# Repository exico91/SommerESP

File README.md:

# 🏠 SommerESP

A plug and play ESP32-C3 board to control Sommer garage doors based on ESPHOME

This combo is designed to replace the Sommer Conex Module and the Sommer Output OC Module. 

> [!TIP]
> **Where to get in touch**
> - 🐛 **Issues:** [report a problem or suggest an improvement](https://github.com/exico91/SommerESP/issues) for the board.
> - 💬 **Discussions:** [ask a question or share a compatibility report](https://github.com/exico91/SommerESP/discussions).

## ⚙️ How it works
The Sommer Conex Module is designed to replicate the press of the buttons on the controller of the garage door and the Sommer Output OC just provide the signal for the status and 24 Volts DC.  

This project takes the 24V and converts it to 3.3V for the ESP32-C3 module, the DC regulator on the power board can take from 4.5V to 40V and cleanly output 3.3V then transfer it to the Control board along with the status signal.  

The ESP controller simulate the press of the buttons using a pair of optocouplers, simple enough. You can also attach other things to this board, I left a couple of GPIOs on exposed pins along with the serial connection required to flash the module.

## 📋 Instructions
You can buy [here](https://www.tindie.com/products/exico91/sommeresp/) the kit that includes the two boards and a cable or you can build one yourself. You can find the BOM (bill of materials) [here](https://htmlpreview.github.io/?https://github.com/exico91/SommerESP/blob/main/Kicad/SommerESP/bom/ibom.html) and the gerber files [here](/Kicad/SommerESP/gerbers/). 
There are a lot of PCB Manufacturers. The most known are [PCBWay](https://www.pcbway.com/) and [JLCPCB](https://jlcpcb.com/). I used both and are good.

### 🔧 Installation
 1. Remove the plug from the wall, or cut off power to the Sommer garage door controller
 2. Write your firmware if you want or use it as is. You can find a basic yaml [here](/ESPHOME/esphome.yaml) or the ethernet module variant [here](/ESPHOME/esphome-eth.yaml). To do so you will need a serial programmer and set it to 3.3V, connect GND, VIN, RX and TX to the controller board and power it on while pressing BOOT on the board. When you are done remove the serial programmer. DO NOT connect the programmer while the board is connected to the power board or inserted in the Sommer controller.
 3. Open the controller but pay attention to the keypad cable when you remove the cover
 4. Place the board as shown, pay attention that both plugs are inserted:

 5. Flip the first two switches to ON on the dip switch array on the Sommer controller
 6. Connect the keypad to the board in the same orientation as it was before (if present, some Sommers do not have a keypad)
 7. Close the cover and power it on. You should be able to see a wifi network and connect to it to configure the module.

> [!NOTE]
> The ethernet module (W5500) yaml is available [here](/ESPHOME/esphome-eth.yaml) and the KiCad project [here](/Kicad/SommerESP-ETHmodule/).

### 📡 External Antenna

If your installation requires better WiFi reception, an external antenna version is available. You will need:
 1. The SommerESP board in the version **without integrated antenna**, available on the [Tindie store](https://www.tindie.com/stores/exico91/)
 2. The **antenna kit** (includes antenna and U.FL adapter cable), also available on the [Tindie store](https://www.tindie.com/stores/exico91/)

Connect the adapter cable to the U.FL connector on the board and attach the external antenna.

### 🛠️ Settings

#### Door position (%)
> [!NOTE]
> This setting require firmware version **3.3** or later.

By default the door is shown only as open or closed. Once the travel times are set, the position is shown as a percentage and the door can be moved to a specific position from Home Assistant.

1. With a stopwatch, measure how long the door takes to open fully (from fully closed) and to close fully (from fully open).
2. In Home Assistant open the SommerESP device page and, under **Configuration**, enter the measured values in **Garage door open time** and **Garage door close time** (in seconds, 0.1 s resolution, up to 120 s). The same fields are available on the ESP web page.
3. Close the door fully once, so the estimated position is aligned with the closed endstop.

The percentage is enabled only when both times are set: set either of them to 0 to go back to plain open/closed. The values are saved on the board and survive reboots. You can also set the defaults directly in the yaml with the `door_open_time` and `door_close_time` substitutions.

> [!TIP]
> The position is estimated from the travel times. If the door is moved with the remote or the wall button, the estimate can drift: it is realigned every time the door closes fully.

Still, this uses an estimated position because the motherboard does not communicate the percentage natively.

### 🔌 Flashing and extra pins
To flash connect you serial programmer to the exposed pins on the controller board. DO NOT connect the programmer while the board is connected to the power board or inserted in the Sommer controller.
From top to bottom the pins are in this order:

3.3V
GPIO05
RX
TX
GPIO18
GPIO19
GPIO03
GND

Press BOOT while powering on the programmer to send the controller in flashing mode.

### 🔄 Factory reset
With the provided yaml, holding the BOOT button for 10 seconds and then releasing it factory resets the board (erases the saved Wi-Fi credentials and preferences, then reboots). It can also be triggered from Home Assistant with the "Factory Reset" button.

## ✅ Compatibility
This project should work with Sommer Base+, Pro+ and Evo+.
The main focus of this project is ESPHome and Homeassistant but you can flash whatever you want on the ESP32-C3.
Check [here](/pinout.md) for the pinout.

**Confirmed working models:**

| **Model**  | **Notes**                                                                                                                                                  | **Credits** |
|------------|------------------------------------------------------------------------------------------------------------------------------------------------------------|-------------|
| 9080 Base+ | The keypad plug is present but there is no keypad, just plug the SommerESP there.                                                                          | tim-kiefer  |
| 2060 Evo+  | The keypad plug has 5 pins instead of 3. Just plug the module on the middle leaving pin 1 and 5 free. See photo for reference [here](/pics/2060+notes.jpg) | Severnt     |
| 9110 Pro+  | Original installation that created this project. This model has a wall mount control board with a 2 button keypad.                                         | Alessio D   |
| S 9050 pro | Need to manually add the DIP switch selector. Check [here](https://github.com/exico91/SommerESP/issues/5#issuecomment-2755661908)                     | M3c4tr0x    |
| A800 XL    | Compatible but the Conex pins are shifted. Requires board version 2 or jumper cables.                                                                    | [jkremlacek](https://github.com/jkremlacek) |

Tested SommerESP on another model? Please share your result in [Discussions](https://github.com/exico91/SommerESP/discussions), whether it worked or not.

> [!WARNING]
> Please do check the distance between the power pins and the right pin on the button connector. This version of SommerESP is compatible with Sommer boards where the distance is around 9.5 mm or 7.5 mm, just check which is correct and solder the connector for the Conex section in the 9.5 (default) or 7.5 place. If you are buying from Tindie the default will be 9.5, if you need 7.5 please contact me.

## 📦 Release Log

### Firmware Release Log

| **Version** | **ESPHome** | **Changes** |
|-------------|-------------|-------------|
| 1.0 | — | Initial release |
| 1.3 | 2024.6.1 | Added compatibility for ESPHome 2024.6.1 |
| 2.0 | 2025.8.3 | Added compatibility for ESPHome 2025.8.3 |
| 3.0 | 2026.5.3 | Added compatibility for ESPHome 2026.5.3+, added Ethernet module version |
| 3.1 | 2026.5.3 | Cover stop function is now working |
| 3.2 | 2026.9.0 | Added factory reset function to the BOOT button (hold for 10 seconds) |
| 3.3 | 2026.10.2 | Added garage door percentage option

### Hardware Release Log

| **Version** | **Changes** |
|-------------|-------------|
| 1.0 - 2.0 | Dual board module with cable |
| 3.0 | Single board, adds Ethernet compatibility. Supports only 9.5 mm distance |
| 3.1 | Adds 7.5 mm distance compatibility |
| 3.2 | Added fabrication holes to the PCB |
| 3.2.1 | Fixed wrong position of J7 |

## 💡 Origins
A thank you to https://github.com/jampez77/garage_door_sensor/ and https://github.com/azrael783/esphome_garagedoor_opener for giving me the ispiration to do this project, a lot of the code and core functionality is similar to these projects. Unfortunately neither did what I needed, cheap and invisible installation. Unfortunately the two Sommer modules (Conex and Output OC) are not cheap for what they are and using a DC-DC converter and relais externally is bulky and unsightly. I took the matter into my hands and now is almost plug and play and places where the two Sommer modules were.

A thank you to [M3c4tr0x](https://github.com/M3c4tr0x) for a part of the design of the new single board.

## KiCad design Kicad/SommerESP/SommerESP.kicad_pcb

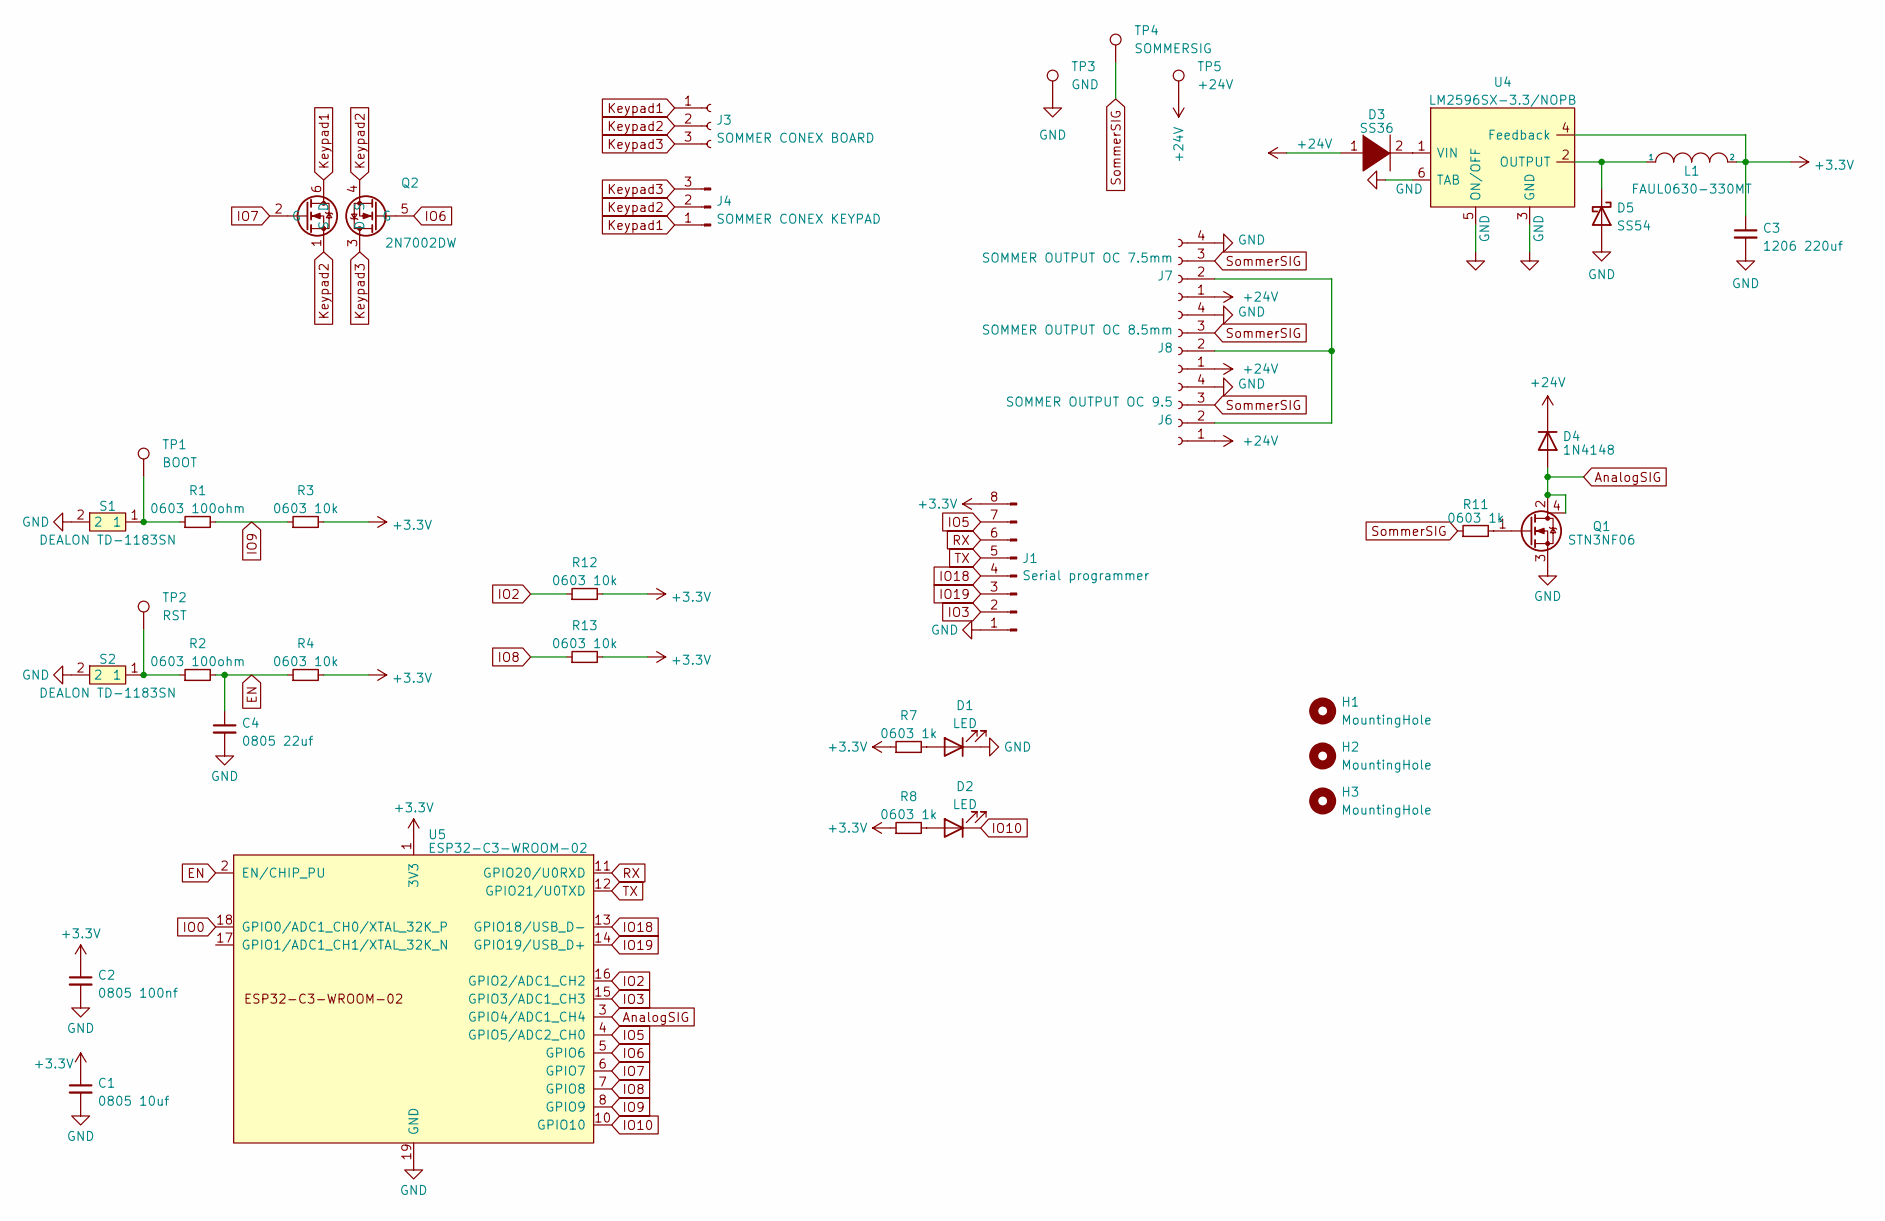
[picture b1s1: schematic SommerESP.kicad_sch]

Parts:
C1: 0805 10uf; C_0805_2012Metric_Pad1.18x1.45mm_HandSolder; LCSC PN C307525
C2: 0805 100nf; C_0805_2012Metric_Pad1.18x1.45mm_HandSolder; LCSC PN C5137467
C3: 1206 220uf; C_1206_3216Metric_Pad1.33x1.80mm_HandSolder; LCSC PN C412252
C4: 0805 22uf; C_0805_2012Metric_Pad1.18x1.45mm_HandSolder; LCSC PN C5674
D1: LED; LED_0805_2012Metric_Pad1.15x1.40mm_HandSolder; LCSC PN C397047
D2: LED; LED_0805_2012Metric_Pad1.15x1.40mm_HandSolder; LCSC PN C497961
D3: SS36; SS32C; LCSC PN C5449114
D4: 1N4148; D_SOD-123; LCSC PN C917030
D5: SS54; D_SMA; LCSC PN C2902914
H1, H2, H3: MountingHole; ToolingHole_1.152mm
J1: Serial programmer; PinHeader_1x08_P2.54mm_Vertical; LCSC PN C6332201
J3: SOMMER CONEX BOARD; PinSocket_1x03_P2.54mm_Vertical; LCSC PN C146243
J4: SOMMER CONEX KEYPAD; PinHeader_1x03_P2.54mm_Vertical; LCSC PN C49257
J6: SOMMER OUTPUT OC 9.5; PinSocket_1x04_P2.54mm_Vertical_SLIT; LCSC PN C2718488
J7: SOMMER OUTPUT OC 7.5mm; PinSocket_1x04_P2.54mm_Vertical_SLIT; LCSC PN C2718488
J8: SOMMER OUTPUT OC 8.5mm; PinSocket_1x04_P2.54mm_Vertical_SLIT; LCSC PN C2718488
L1: FAUL0630-330MT; L_Abracon_ASPI-0630LR; LCSC PN C7461364
Q1: STN3NF06; STN3NF06L; LCSC PN C222218
Q2: 2N7002DW; SOT-363_SC-70-6; LCSC PN C5190214
R1, R2: 0603 100ohm; R_0603_1608Metric_Pad0.98x0.95mm_HandSolder; LCSC PN C3017758
R3, R4, R12, R13: 0603 10k; R_0603_1608Metric_Pad0.98x0.95mm_HandSolder; LCSC PN C2930027
R7, R8, R11: 0603 1k; R_0603_1608Metric_Pad0.98x0.95mm_HandSolder; LCSC PN C116692
S1, S2: DEALON TD-1183SN; DEALON TD-1183SN-1.5H-160; LCSC PN C2905192
TP1: BOOT; TestPoint_Pad_2.0x2.0mm
TP2: RST; TestPoint_Pad_2.0x2.0mm
TP3: GND; TestPoint_Pad_D2.0mm
TP4: SOMMERSIG; TestPoint_Pad_D2.0mm
TP5: +24V; TestPoint_Pad_D2.0mm
U4: LM2596SX-3.3/NOPB; TO-263-5_TabPin3; LCSC PN C5186052
U5: ESP32-C3-WROOM-02; LCSC PN C2934560

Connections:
+3.3V: C1.1, C2.1, C3.1, J1.8, L1.2, R3.2, R4.2, R7.1, R8.1, R12.2, R13.2, U4.4 (Feedback), U5.1 (3V3)
+24V: D3.1 (K), D4.1 (K), J6.1, J7.1, J8.1, TP5.1 (1_1)
AnalogSIG: D4.2 (A), Q1.2 (D), Q1.4 (D_TAB), U5.3 (GPIO4/ADC1_CH4)
EN: C4.1, R2.2, R4.1, U5.2 (EN/CHIP_PU)
GND: C1.2, C2.2, C3.2, C4.2, D1.1 (K), D5.2 (A), J1.1, J6.4, J7.4, J8.4, Q1.3 (S), S1.2, S2.2, TP3.1 (1_1), U4.3 (GND), U4.5 (ON/OFF), U4.6 (TAB), U5.9 (GND), U5.19 (GND)
IO0: U5.18 (GPIO0/ADC1_CH0/XTAL_32K_P)
IO2: R12.1, U5.16 (GPIO2/ADC1_CH2)
IO3: J1.2, U5.15 (GPIO3/ADC1_CH3)
IO5: J1.7, U5.4 (GPIO5/ADC2_CH0)
IO6: Q2.5 (G), U5.5 (GPIO6)
IO7: Q2.2 (G), U5.6 (GPIO7)
IO8: R13.1, U5.7 (GPIO8)
IO9: R1.2, R3.1, U5.8 (GPIO9)
IO10: D2.1 (K), U5.10 (GPIO10)
IO18: J1.4, U5.13 (GPIO18/USB_D-)
IO19: J1.3, U5.14 (GPIO19/USB_D+)
Keypad1: J3.1, J4.1, Q2.6 (D)
Keypad2: J3.2, J4.2, Q2.1 (S), Q2.4 (S)
Keypad3: J3.3, J4.3, Q2.3 (D)
unnamed: D1.2 (A), R7.2
unnamed: D2.2 (A), R8.2
unnamed: D3.2 (A), U4.1 (VIN)
unnamed: D5.1 (K), L1.1, U4.2 (OUTPUT)
unnamed: J6.2, J7.2, J8.2
unnamed: Q1.1 (G), R11.2
unnamed: R1.1, S1.1, TP1.1 (1_1)
unnamed: R2.1, S2.1, TP2.1 (1_1)
RX: J1.6, U5.11 (GPIO20/U0RXD)
SommerSIG: J6.3, J7.3, J8.3, R11.1, TP4.1 (1_1)
TX: J1.5, U5.12 (GPIO21/U0TXD)

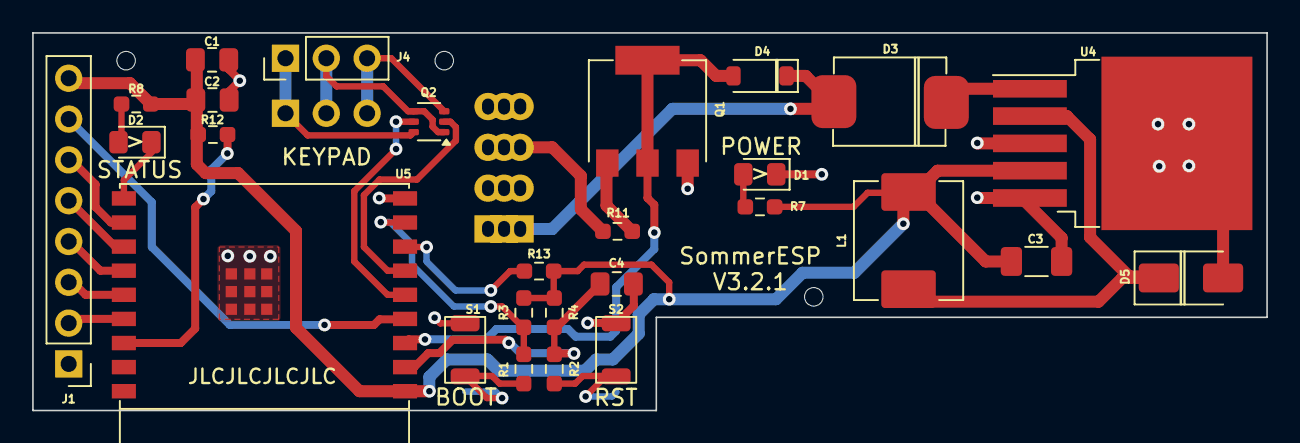
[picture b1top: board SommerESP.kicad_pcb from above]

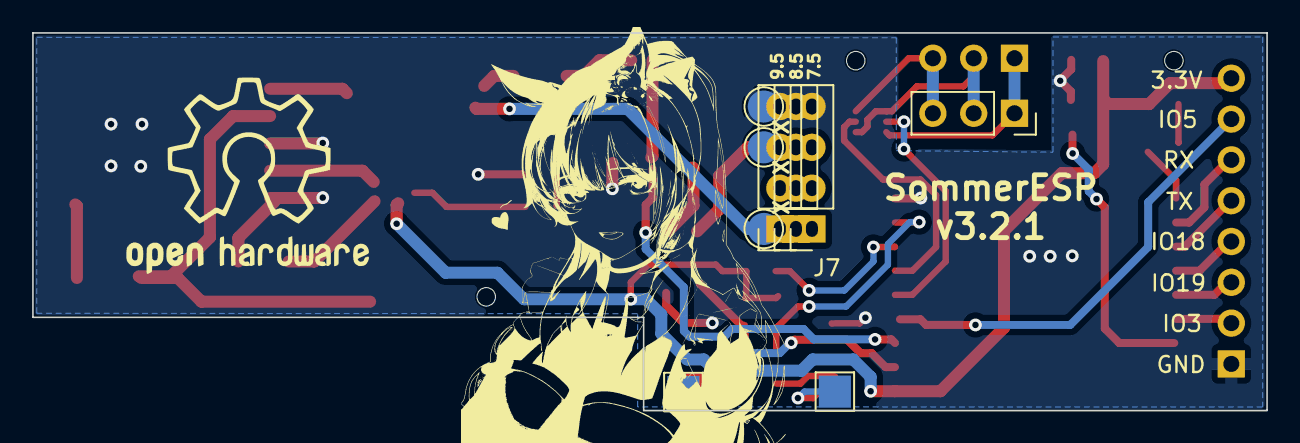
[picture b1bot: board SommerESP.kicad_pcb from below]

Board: 2 copper layers, 76.8 x 23.5 mm, 39 parts (9 on the bottom side), 29 nets.

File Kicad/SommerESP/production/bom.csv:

Designator,Footprint,Quantity,Value,LCSC Part #
C1,0805,1,0805 10uf,C412252
C2,0805,1,0805 100nf,C412252
C3,1206,1,1206 220uf,C412252
C4,0805,1,0805 22uf,C412252
D1,0805,1,LED Green,C397047
D2,0805,1,LED Blue,C497961
D3,SS32C,1,SS36,C5449114
D4,D_SOD-123,1,1N4148,C402212
D5,D_SMA,1,SS54,C2902914
J1,PinHeader_1x08_P2.54mm_Vertical,1,Serial programmer,C6332201
J3,PinSocket_1x03_P2.54mm_Vertical,1,SOMMER CONEX BOARD,C146243
J4,PinHeader_1x03_P2.54mm_Vertical,1,SOMMER CONEX KEYPAD,C49257
J6,PinSocket_1x04_P2.54mm_Vertical,1,SOMMER OUTPUT OC,C2718488
L1,L_Abracon_ASPI-0630LR,1,FAUL0630-330MT,C7461364
Q1,STN3NF06L,1,STN3NF06,C222218
Q2,SOT-363_SC-70-6,1,2N7002DW,C5190214
"R1, R2",0603,2,0603 100ohm,C3017758
"R11, R7, R8",0603,3,0603 1k,C116692
"R12, R13, R3, R4",0603,4,0603 10k,C2930027
"S1, S2",DEALON TD-1183SN-1.5H-160,2,DEALON TD-1183SN,C2905192
U4,TO-263-5_TabPin3,1,LM2596SX-3.3/NOPB,C5186052
U5,ESP32-C3-WROOM-02,1,ESP32-C3-WROOM-02,C2934560

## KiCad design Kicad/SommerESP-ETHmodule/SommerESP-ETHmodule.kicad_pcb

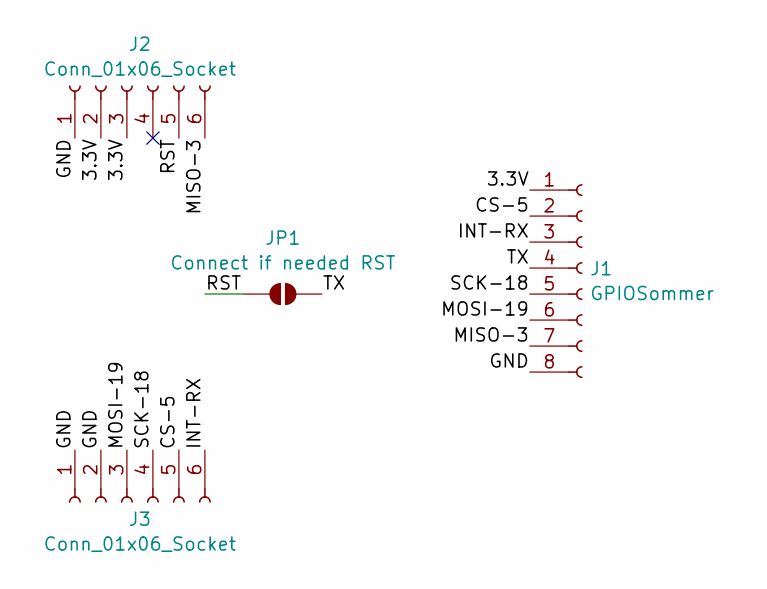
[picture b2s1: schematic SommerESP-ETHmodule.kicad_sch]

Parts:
J1: GPIOSommer; PinSocket_1x08_P2.54mm_Vertical
J2, J3: Conn_01x06_Socket; PinSocket_1x06_P2.54mm_Vertical
JP1: Connect if needed RST; SolderJumper-2_P1.3mm_Open_RoundedPad1.0x1.5mm

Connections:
/3.3V: J1.1, J2.2, J2.3
/CS-5: J1.2, J3.5
/GND: J1.8, J2.1, J3.1, J3.2
/INT-RX: J1.3, J3.6
/MISO-3: J1.7, J2.6
/MOSI-19: J1.6, J3.3
/RST: J2.5, JP1.1 (A)
/SCK-18: J1.5, J3.4
/TX: J1.4, JP1.2 (B)

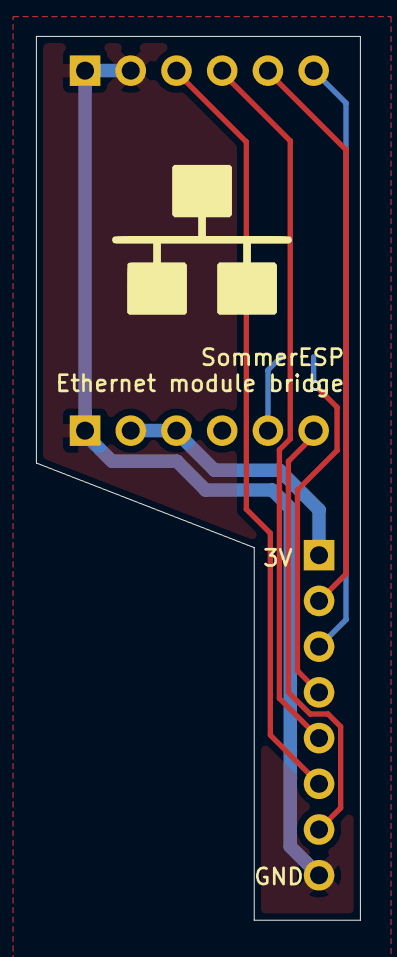
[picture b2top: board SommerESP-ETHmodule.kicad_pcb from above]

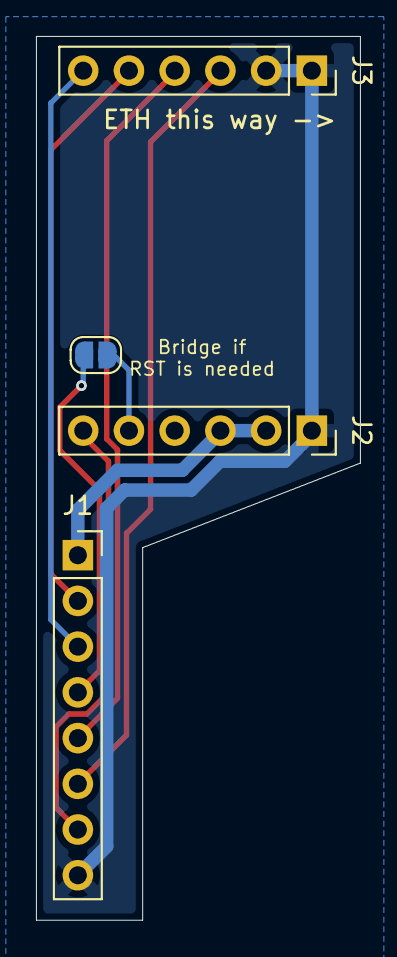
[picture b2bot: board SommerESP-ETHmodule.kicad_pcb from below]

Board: 2 copper layers, 18.0 x 49.1 mm, 4 parts (4 on the bottom side), 9 nets.

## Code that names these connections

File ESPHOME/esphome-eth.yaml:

esphome:
  name: sommeresp-eth
  name_add_mac_suffix: true
  project:
    name: "esphome.sommeresp"
    version: "3.3"

substitutions:
  device_name: "SommerESP"
  hotspot_password: "sommeresp"
  webserver_password: "sommeresp"

  project_name: "SommerESP by exico91"
  project_version: "3.3"

  # Full travel times of the door in seconds, used to estimate its position
  # in %. 0 = not configured: the door is shown only as open/closed. Measure
  # them with a stopwatch; they can also be set later from Home Assistant
  # (Garage door open/close time). The percentage works only when both are set.
  door_open_time: "0"
  door_close_time: "0"


esp32:
  board: esp32-c3-devkitm-1
  framework:
    type: arduino


# Enable logging
logger:

# Enable Home Assistant API
api:

ota:
  - platform: esphome

ethernet:
  type: W5500
  clk_pin: GPIO18
  mosi_pin: GPIO19
  miso_pin: GPIO3
  cs_pin: GPIO5
  interrupt_pin: GPIO20

# Optional Static IP
#  manual_ip: 
#    static_ip: 192.168.1.60
#    gateway: 192.168.1.1
#    subnet: 255.255.255.0
    
# Enable Web server (optional).
web_server:
  port: 80

# Uncomment to setup user and password for the dashboard
#  auth:
#    username: "admin"
#    password: ${webserver_password}


text_sensor:
  # Expose ESPHome version as sensor.
  - platform: version
    name: ${device_name} ESPHome Version
  # Expose Ethernet information
  - platform: ethernet_info
    ip_address:
      name: ESP IP Address 
    dns_address: 
      name: ESP DNS Address
    mac_address: 
      name: ESP MAC Address
    
sensor:
  - platform: uptime
    name: ${device_name} Uptime
  - platform: adc
    pin: 4
    name: "Door Feedback"
    update_interval: 500ms
    id: status_feedback
    internal: True

binary_sensor:
  # ON when the door is fully closed: used as the close endstop of the cover.
  - platform: analog_threshold
    name: "Door closed"
    sensor_id: status_feedback
    threshold: 0.015
    id: door_closed
    internal: True
    on_release:
      # The door left the closed position without a command from us (remote,
      # wall button): its movement can't be tracked, so assume fully open.
      - lambda: |-
          if (id(garage_door).current_operation == COVER_OPERATION_IDLE) {
            id(garage_door).position = COVER_OPEN;
            id(garage_door).publish_state();
          }

  # BOOT button: hold for 10s to factory reset. It acts on release, so the
  # reboot never happens with GPIO9 held low (which would enter download mode).
  - platform: gpio
    pin:
      number: GPIO9
      mode: INPUT_PULLUP
      inverted: true
    id: boot_button
    internal: true
    on_click:
      min_length: 10s
      max_length: 60s
      then:
        - button.press: factory_reset_button

globals:
  - id: last_direction
    type: int
    restore_value: no
    initial_value: '0'  # 0=idle, 1=opening, 2=closing
  - id: move_start
    type: uint32_t
    restore_value: no
    initial_value: '0'  # millis() of the last open/close pulse

number:
  - platform: template
    name: "Garage door open time"
    id: open_time
    entity_category: config
    unit_of_measurement: s
    mode: box
    min_value: 0
    max_value: 120
    step: 0.1
    optimistic: true
    restore_value: true
    initial_value: ${door_open_time}
    on_value:
      - script.execute: apply_travel_times
  - platform: template
    name: "Garage door close time"
    id: close_time
    entity_category: config
    unit_of_measurement: s
    mode: box
    min_value: 0
    max_value: 120
    step: 0.1
    optimistic: true
    restore_value: true
    initial_value: ${door_close_time}
    on_value:
      - script.execute: apply_travel_times

script:
  # With both travel times set, the cover estimates the position from them.
  # Otherwise it moves instantly: open is shown as soon as the door is commanded
  # to open, closed when the status input reports it, as before.
  - id: apply_travel_times
    then:
      - lambda: |-
          bool timed = id(open_time).state > 0 && id(close_time).state > 0;
          id(garage_door).set_open_duration(timed ? id(open_time).state * 1000 : 1);
          id(garage_door).set_close_duration(timed ? id(close_time).state * 1000 : 1);

switch:
  - platform: gpio
    pin: 
      number: 7
      #inverted: True
    name: "Garage door Open Switch"
    id: open_switch
    on_turn_on:
      - delay: 250ms
      - switch.turn_off: open_switch
    restore_mode: ALWAYS_OFF
  - platform: gpio
    pin: 
      number: 6
      #inverted: True
    name: "Garage door close Switch"
    id: close_switch
    on_turn_on:
      - delay: 250ms
      - switch.turn_off: close_switch
    restore_mode: ALWAYS_OFF
  - platform: restart
    name: "Restart ESP"

button:
  - platform: factory_reset
    name: "Factory Reset"
    id: factory_reset_button
    entity_category: diagnostic

cover:
  # Time based cover: the position is estimated from the travel times, and
  # setting a position sends a stop pulse when the estimate reaches it.
  - platform: feedback
    id: garage_door
    device_class: garage
    name: "Garage door"
    # Set at boot from the travel time numbers (apply_travel_times).
    open_duration: 1ms
    close_duration: 1ms
    close_endstop: door_closed
    # The Sommer stops by itself at the ends, never send a stop there.
    has_built_in_endstop: true
    # Reversing while moving: stop first, then start the other way.
    direction_change_wait_time: 1s
    # Give up waiting for the close endstop (e.g. the door reversed on an obstacle).
    max_duration: 150s
    open_action:
      - globals.set:
          id: last_direction
          value: '1'
      - lambda: 'id(move_start) = millis();'
      - switch.turn_off: close_switch
      - switch.turn_on: open_switch
    close_action:
      - globals.set:
          id: last_direction
          value: '2'
      - lambda: 'id(move_start) = millis();'
      - switch.turn_off: open_switch
      - switch.turn_on: close_switch
    # The Sommer stops when it gets another pulse in the direction it is moving.
    # Only pulse while the motor can still be moving: after the full travel time
    # (120s without travel times) it has stopped by itself, and a pulse would
    # start it again.
    stop_action:
      - lambda: |-
          if (id(last_direction) == 0)
            return;
          bool opening = id(last_direction) == 1;
          switch_::Switch *relay = opening ? id(open_switch) : id(close_switch);
          // The command pulse is still on: the stop came right after the command
          // (target already reached without travel times), keep moving.
          if (relay->state)
            return;
          bool timed = id(open_time).state > 0 && id(close_time).state > 0;
          float travel = timed ? (opening ? id(open_time).state : id(close_time).state) : 120;
          if (millis() - id(move_start) < travel * 1000)
            relay->turn_on();
          id(last_direction) = 0;

status_led:
  pin:
    number: 10
    inverted: true
    

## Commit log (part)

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2023-10-09 First upload
2023-10-09 Added instructions
2023-10-21 Updated description and yaml
2023-10-26 removed backups
    inverted up and down pins after testing
2023-11-16 Update README.md
    added link to shop
2023-12-04 Update esphome.yaml
    Added some options and better device naming
2024-01-13 Found an error in the schematic for Diode D4. Was inverted in the schematic but correct in the PCB and Photos.
    Thank you to Stefano Gnocato for pointing that out!
2024-01-25 Updated the check for door status from analog threshold to gpio with a pullup. This should be less prone to error and free some computational power
    Thanks to Stefano Gnocato for the input!
2024-03-17 Updated ota and api, cleaned the code a bit.
2024-05-08 Updated Kicad to version 8 Added references to LCSC part numbers in the project and BOM Cleaned up a bit of silkscreen text and added some references Added JLCJLCJLCJLC on the silkscreen for the orde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
2024-06-21 Compatibility with esphome 2024.6.1 +
2025-06-25 Added gitignore to ignore backups Added default config for ibom
2025-09-06 Updated to V2. This is a transition version.
    Updated yaml and added M3c4tr0x confirmation of
    board working
2025-09-06 misspell
2025-10-23 Version 3.0 of SommerESP
2026-06-10 - Add W5500 ethernet ESPHome config (esphome-eth.yaml) - Split KiCad project into SommerESP/ and SommerESP-ETHmodule/ - Update README: emojis, ethernet yaml link, external antenna instructions
2026-06-10 Update README with A800 XL compatibility details
    Added compatibility note for A800 XL model regarding Conex pin shift and board version requirements.
2026-06-11 - Cover stop function is now working - Added a release log in the README.md
